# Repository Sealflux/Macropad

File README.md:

# Sealflux

An 8-key macropad with OLED, rotary encoder, and RGB LEDs. Powered by a Seeed XIAO RP2040 running KMK firmware.

## Features
- 7 Cherry MX switches + 1 rotary encoder (with pushbutton)
- 5 layers: Main, Media, Home Assistant, Game, Other
- Rotary encoder for volume and scrolling
- 128x64 OLED display showing current layer
- WS2812 RGB LEDs with animations
- KMK firmware (CircuitPython)

## Hardware
- Seeed XIAO RP2040
- 7x Cherry MX switches
- 1x EC11 rotary encoder
- 1x SSD1306 128x64 OLED
- 7x WS2812 RGB LEDs
- 3D-printed case (top + bottom)

## BOM
| Part | Quantity | Notes |
|------|----------|-------|
| Seeed XIAO RP2040 | 1 | |
| Cherry MX switches | 7 | |
| EC11 rotary encoder | 1 | |
| SSD1306 OLED 128x64 | 1 | I2C |
| WS2812 LEDs | 7 | |
| 1N4148 diodes | 7 | |
| M2 screws | 4 | |
| 3D-printed case | 1 set | top + bottom |

## Pinout
| Function | XIAO Pin | GPIO |
|----------|----------|------|
| Col 0 | D0 | GP0 |
| Col 1 | D1 | GP1 |
| Col 2 | D2 | GP2 |
| Col 3 | D3 | GP3 |
| SDA | D4 | GP4 |
| SCL | D5 | GP5 |
| Row 0 | D6 | GP6 |
| Enc A | D7 | GP7 |
| Enc B | D8 | GP8 |
| Row 1 | D9 | GP9 |
| LED | D10 | GP10 |

## Firmware
KMK (CircuitPython). To install, copy `main.py` and the KMK library folder to the XIAO RP2040 after flashing CircuitPython.

## Schematic

## PCB

## Case

## Photos
[Add photos after assembly]

## Demo
[Add video link after assembly]

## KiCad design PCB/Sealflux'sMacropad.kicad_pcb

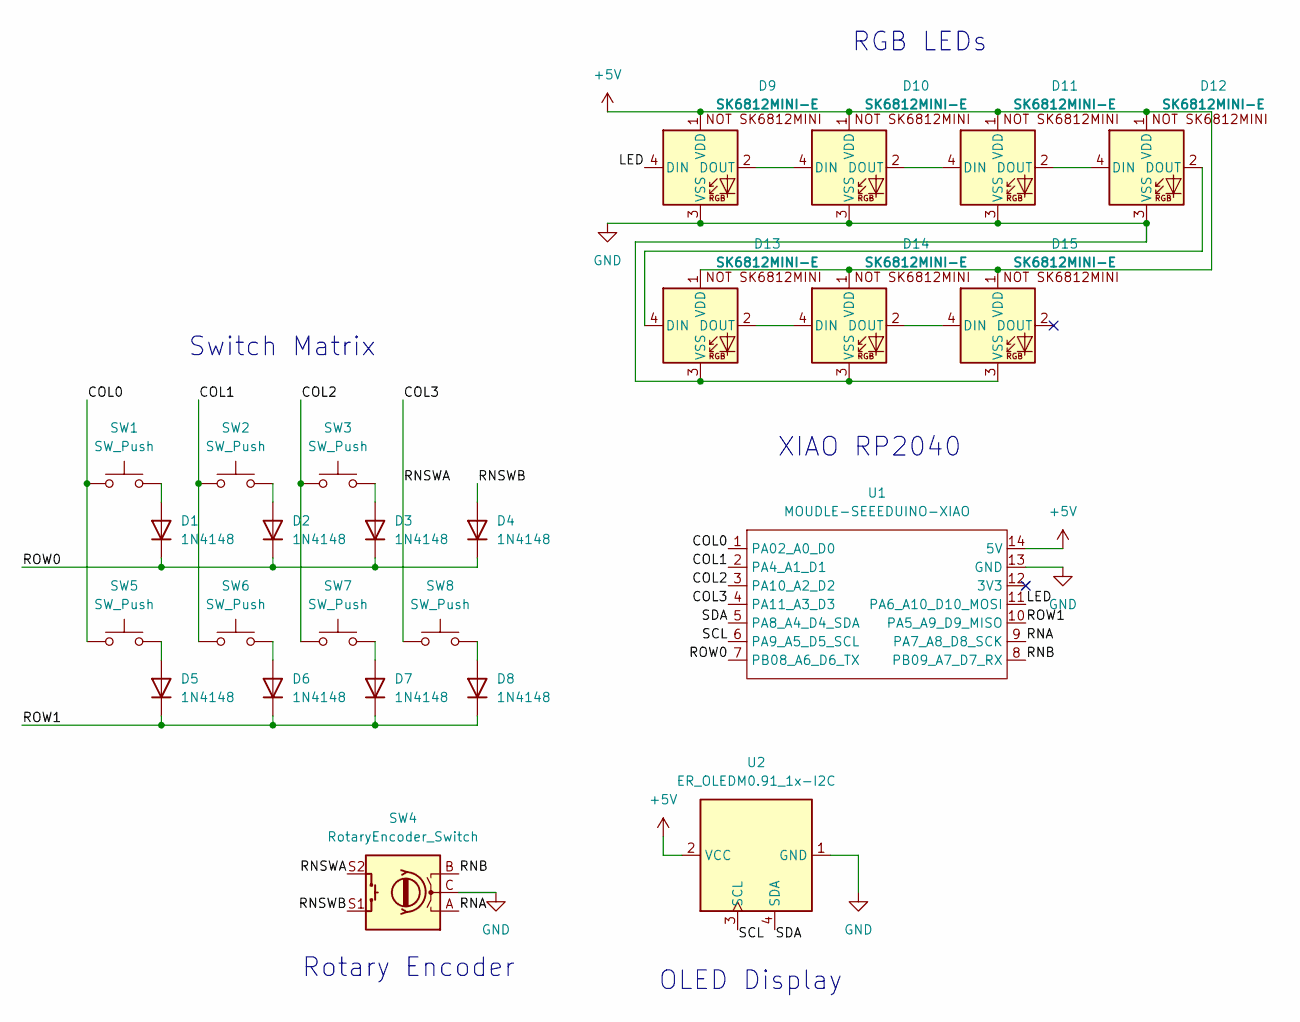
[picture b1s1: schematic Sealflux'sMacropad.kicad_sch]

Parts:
D1, D2, D3, D4, D5, D6, D7, D8: 1N4148; D_DO-35_SOD27_P7.62mm_Horizontal
D9, D10, D11, D12, D13, D14, D15: SK6812MINI-E; SK6812MINI-E_fixed
SW1, SW2, SW3, SW5, SW6, SW7, SW8: SW_Push; SW_Cherry_MX_1.00u_PCB
SW4: RotaryEncoder_Switch; RotaryEncoder_Alps_EC11E-Switch_Vertical_H20mm_CircularMoun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
U1: MOUDLE-SEEEDUINO-XIAO; XIAO-Generic-Hybrid-14P-2.54-21X17.8MM
U2: ER_OLEDM0.91_1x-I2C; SSD1306-0.91-OLED-4pin-128x32

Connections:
+5V: D9.1 (VDD), D10.1 (VDD), D11.1 (VDD), D12.1 (VDD), D13.1 (VDD), D14.1 (VDD), D15.1 (VDD), U1.14 (5V), U2.2 (VCC)
/COL0: SW1.1, SW5.1, U1.1 (PA02_A0_D0)
/COL1: SW2.1, SW6.1, U1.2 (PA4_A1_D1)
/COL2: SW3.1, SW7.1, U1.3 (PA10_A2_D2)
/COL3: SW4.S2, SW8.1, U1.4 (PA11_A3_D3)
/LED: D9.4 (DIN), U1.11 (PA6_A10_D10_MOSI)
/RNA: SW4.A, U1.9 (PA7_A8_D8_SCK)
/RNB: SW4.B, U1.8 (PB09_A7_D7_RX)
/RNSWB: D4.2 (A), SW4.S1
/ROW0: D1.1 (K), D2.1 (K), D3.1 (K), D4.1 (K), U1.7 (PB08_A6_D6_TX)
/ROW1: D5.1 (K), D6.1 (K), D7.1 (K), D8.1 (K), U1.10 (PA5_A9_D9_MISO)
/SCL: U1.6 (PA9_A5_D5_SCL), U2.3 (SCL)
/SDA: U1.5 (PA8_A4_D4_SDA), U2.4 (SDA)
GND: D9.3 (VSS), D10.3 (VSS), D11.3 (VSS), D12.3 (VSS), D13.3 (VSS), D14.3 (VSS), D15.3 (VSS), SW4.C, U1.13 (GND), U2.1 (GND)
unnamed: D1.2 (A), SW1.2
unnamed: D2.2 (A), SW2.2
unnamed: D3.2 (A), SW3.2
unnamed: D5.2 (A), SW5.2
unnamed: D6.2 (A), SW6.2
unnamed: D7.2 (A), SW7.2
unnamed: D8.2 (A), SW8.2
unnamed: D9.2 (DOUT), D10.4 (DIN)
unnamed: D10.2 (DOUT), D11.4 (DIN)
unnamed: D11.2 (DOUT), D12.4 (DIN)
unnamed: D12.2 (DOUT), D13.4 (DIN)
unnamed: D13.2 (DOUT), D14.4 (DIN)
unnamed: D14.2 (DOUT), D15.4 (DIN)

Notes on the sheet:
RGB LEDs
Switch Matrix
OLED Display
XIAO RP2040
Rotary Encoder

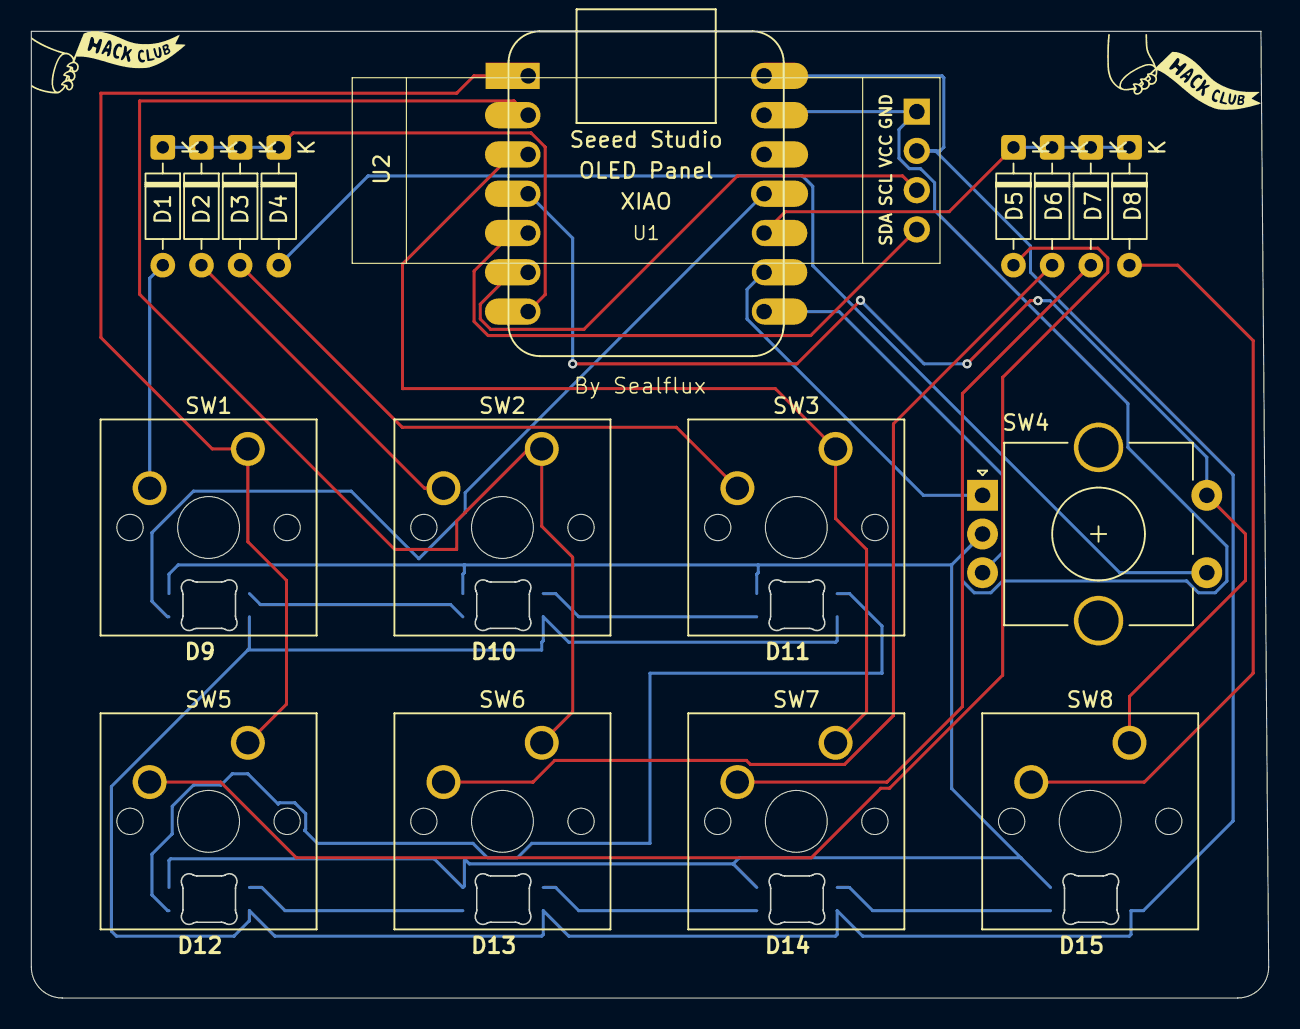
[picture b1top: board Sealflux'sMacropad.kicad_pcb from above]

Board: 2 copper layers, 80.0 x 62.5 mm, 25 parts (0 on the bottom side), 27 nets.

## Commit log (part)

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2026-06-24 Day 1 Shell/Skeleton
